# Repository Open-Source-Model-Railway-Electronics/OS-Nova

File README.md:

# OS-Nova

Initial repository skeleton.

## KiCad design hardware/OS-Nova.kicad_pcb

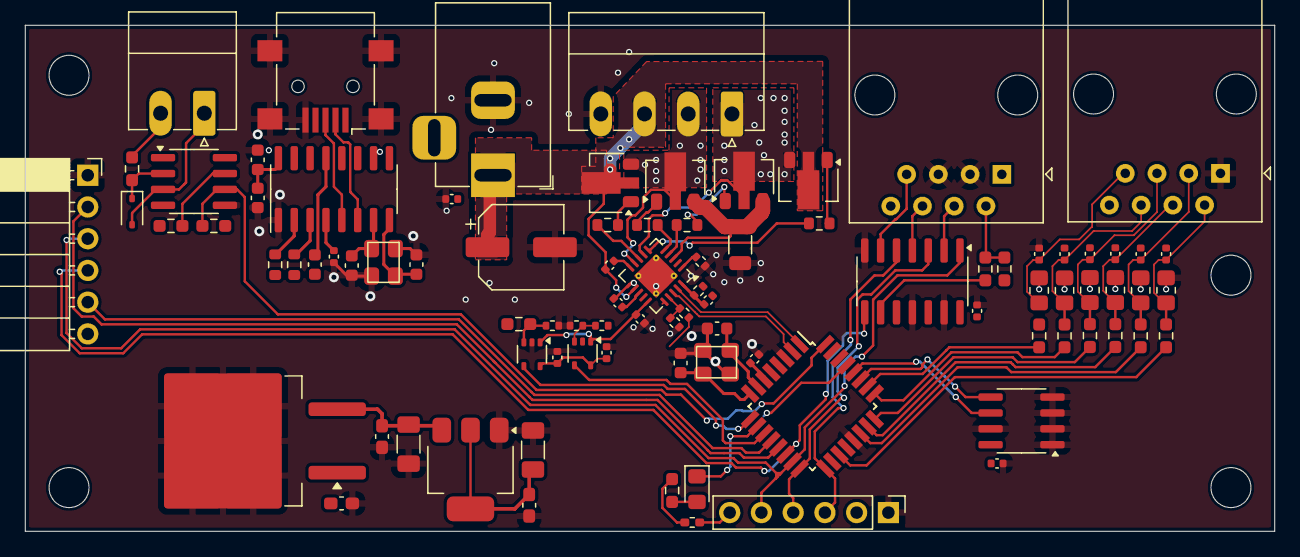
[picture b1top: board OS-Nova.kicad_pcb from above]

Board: 2 copper layers, 100.0 x 40.5 mm, 90 parts (0 on the bottom side), 73 nets.

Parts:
C201, C203: 12pF; C_0603_1608Metric
C202, C301, C501, C502, C503, C505, C506, C508, C604, C705, C707, C1001, C1201, C1301, C1401, C1801: 100nF; C_0402_1005Metric
C504: 1nF; C_0402_1005Metric
C507: 100uF; CP_Elec_6.3x7.7
C602, C802: 100nF; C_0603_1608Metric_Pad1.08x0.95mm_HandSolder
C603, C803: 100uF; C_1206_3216Metric_Pad1.33x1.80mm_HandSolder
C701: 10uF; C_0603_1608Metric
C702, C706: 100nF; C_0603_1608Metric
C703, C704: 22pF; C_0603_1608Metric
C801: 330nF; C_0603_1608Metric_Pad1.08x0.95mm_HandSolder
D201: LED; LED_0805_2012Metric_Pad1.15x1.40mm_HandSolder
D1701: 1N4148WS; D_SOD-323
J202: ICSP; PinHeader_1x06_P2.54mm_Vertical
J301, J401: RJ45; RJ45_Amphenol_54602-x08_Horizontal
J501: Screw_Terminal_01x04; PhoenixContact_MC_1,5_4-G-3.5_1x04_P3.50mm_Horizontal
J601: Jack-DC; BarrelJack_Horizontal
J701: USB_B_Mini; USB_Mini-B_Lumberg_2486_01_Horizontal
J901: Conn_01x06_Socket; PinSocket_1x06_P2.54mm_Horizontal
J1701: Screw_Terminal_01x02; PhoenixContact_MC_1,5_2-G-3.5_1x02_P3.50mm_Horizontal
Q501, Q502, Q503, Q504: TM10N06SI; SOT-89-3
R201: 6k2; R_0603_1608Metric_Pad0.98x0.95mm_HandSolder
R202: 10k; R_0402_1005Metric_Pad0.72x0.64mm_HandSolder
R301: 100R; R_0603_smalltext
R302: 4k7; R_0603_smalltext
R501, R502, R503, R504: 10R; R_0603_1608Metric
R505, R510: 22k; R_0402_1005Metric
R506: 10m; R_1206_3216Metric
R507: 150k; R_0402_1005Metric
R508, R512: 10k; R_0402_1005Metric
R509, R513: 1k; R_0402_1005Metric
R511: 62k; R_0603_smalltext
R601, R703, R1001, R1201, R1301, R1401: 1k; R_0603_smalltext
R602, R704, R1002, R1202, R1302, R1402: 250R; R_0805_handsolder-smalltext
R701, R702: 1k; R_0603_1608Metric
R1701, R1702: 10k; R_0603_smalltext
R1703: 1k5; R_0603_smalltext
U202: ATmega328-A; TQFP-32_7x7mm_P0.8mm
U301: 74HC14; SOIC-14_3.9x8.7mm_P1.27mm
U501: A4955; QFN-20-1EP_4x4mm_P0.5mm_EP2.5x2.5mm_ThermalVias
U502, U503: LMV321; SOT-353_SC-70-5
U701: CH340G; SOIC-16_3.9x9.9mm_P1.27mm
U801: L7812; TO-263-2
U802: AMS1117-5.0; SOT-223-3_TabPin2
U1701: HCPL-0601; SOIC-8_3.9x4.9mm_P1.27mm
U1801: 24LC256; SOIC-8_3.9x4.9mm_P1.27mm
Y201: Crystal_GND2; crystal_arduino
Y701: Crystal; crystal_arduino

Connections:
+5V: C202.1, C301.1, C503.2, C505.2, C602.1, C603.1, C701.1, C702.1, C1801.1, J202.2, J901.6, R201.1, R202.1, R302.1, R507.1, R509.1, R511.1, R1701.1, R1702.1, U202.4 (VCC), U202.6 (VCC), U202.18 (AVCC), U301.14 (VCC), U501.2 (SLEEPn), U502.5 (V+), U503.5 (V+), U701.16 (VCC), U802.2 (VO), U1701.8 (VCC), U1801.8 (VCC)
+12V: C802.1, C803.1, J301.1, J401.8, U801.3 (OUT), U802.3 (VI)
/CPU/CURRENT: U202.11 (PD7), U502.4
/CPU/DCC_TTL: R1701.2, U202.32 (PD2), U1701.6 (VO)
/CPU/J: U202.2 (PD4), U501.18 (IN2)
/CPU/K: U202.1 (PD3), U501.19 (IN1)
/CPU/LED: D201.1 (K), U202.10 (PD6)
/CPU/P1: R1001.1, U202.19 (ADC6)
/CPU/P2: R601.1, U202.22 (ADC7)
/CPU/P3: R703.1, U202.23 (PC0)
/CPU/P4: R1201.1, U202.24 (PC1)
/CPU/P5: R1301.1, U202.25 (PC2)
/CPU/P6: R1401.1, U202.26 (PC3)
/CPU/PL: J202.4, U202.16 (PB4), U301.3
/CPU/Reset: C706.2, J202.6, R202.2, U202.29 (~RESET/PC6)
/CPU/Rx: R701.2, U202.30 (PD0)
/CPU/S88RESET: J202.3, U202.17 (PB5), U301.5
/CPU/SCL: U202.28 (PC5), U1801.6 (SCL)
/CPU/SDA: U202.27 (PC4), U1801.5 (SDA)
/CPU/SHORT: U202.9 (PD5), U503.4
/CPU/Tx: R702.1, U202.31 (PD1)
/CPU/X1: C201.2, U202.7 (XTAL1/PB6), Y201.1
/CPU/X2: C203.2, U202.8 (XTAL2/PB7), Y201.3
/CPU/clock: J202.5, J901.3, U202.15 (PB3), U301.1
/CPU/in_next: J901.4, U202.14 (PB2), U301.8
/CPU/latch: J901.2, U202.13 (PB1)
/CPU/out_next: J901.5, U202.12 (PB0)
/DCC/AIOUT: C502.1, U501.15 (AIOUT), U502.1 (+), U503.1 (+)
/DCC/DCC_A: J501.2, Q501.3 (S), Q502.2 (D), U501.9 (SA)
/DCC/DCC_B: J501.1, Q503.3 (S), Q504.2 (D), U501.7 (SB)
/DCC/G_left_H: Q501.1 (G), R502.2
/DCC/G_left_L: Q502.1 (G), R501.2
/DCC/G_right_H: Q503.1 (G), R504.2
/DCC/G_right_L: Q504.1 (G), R503.2
/DCC/RETOUR: Q502.3 (S), Q504.3 (S), R506.1, U501.3 (SENSE)
/throttle/I-V-1/current: C1001.1, J401.2, R1001.2, R1002.1
/throttle/I-V-2/current: C604.1, J401.3, R601.2, R602.1
/throttle/I-V-3/current: C707.1, J401.4, R703.2, R704.1
/throttle/I-V-4/current: C1201.1, J401.5, R1201.2, R1202.1
/throttle/I-V-5/current: C1301.1, J401.6, R1301.2, R1302.1
/throttle/I-V-6/current: C1401.1, J401.7, R1401.2, R1402.1
GND: C201.1, C202.2, C203.1, C301.2, C502.2, C503.1, C504.1, C505.1, C506.2, C507.2, C602.2, C603.2, C604.2, C701.2, C702.2, C703.2, C704.2, C705.1, C707.2, C801.2, C802.2, C803.2, C1001.2, C1201.2, C1301.2, C1401.2, C1801.2, J202.1, J301.3, J301.5, J401.1, J501.4, J601.2, J701.5 (GND), J701.6 (Shield), J901.1, R505.2, R506.2, R508.2, R510.1, R512.2, R513.2, R602.2, R704.2, R1002.2, R1202.2, R1302.2, R1402.2, U202.3 (GND), U202.5 (GND), U202.21 (GND), U301.7 (GND), U301.11, U301.13, U501.14 (GND), U501.21 (GND), U502.2 (V-), U503.2 (V-), U701.1 (GND), U801.2 (GND), U802.1 (GND), U1701.5 (GND), U1801.1 (A0), U1801.2 (A1), U1801.3 (A2), U1801.4 (GND), U1801.7 (WP), Y201.2 (GND), Y201.4 (GND), Y701.2 (GND), Y701.4 (GND)
unnamed: D201.2 (A), R201.2
unnamed: D1701.2 (A), J1701.1, U1701.3 (C)
unnamed: D1701.1 (K), R1703.2, U1701.2 (A)
unnamed: J301.2, R301.2, R302.2
unnamed: J301.4, U301.2
unnamed: J301.6, U301.4
unnamed: J301.7, U301.6
unnamed: J701.3 (D+), U701.5 (UD+)
unnamed: J701.2 (D-), U701.6 (UD-)
unnamed: J1701.2, R1703.1
unnamed: R301.1, U301.9
unnamed: C508.2, U501.13 (CP1)
unnamed: C508.1, U501.11 (CP2)
unnamed: R502.1, U501.8 (GH_A)
unnamed: R504.1, U501.6 (GH_B)
unnamed: R501.1, U501.5 (GL_A)
unnamed: R503.1, U501.4 (GL_B)
unnamed: R505.1, U501.1 (Iset)
unnamed: C504.2, R510.2, U501.20 (RC)
unnamed: C501.1, U501.10 (VCP)
unnamed: R509.2, R513.1, U501.17 (VREF)
unnamed: R507.2, R508.1, U502.3 (-)
unnamed: R511.2, R512.1, U503.3 (-)
unnamed: R702.2, U701.3 (RXD)
unnamed: R701.1, U701.2 (TXD)
unnamed: C705.2, U701.4 (V3)
unnamed: C703.1, U701.7 (XI), Y701.1
unnamed: C704.1, U701.8 (XO), Y701.3
unnamed: C706.1, U701.13 (~DTR)
unnamed: R1702.2, U1701.7 (EN)
VCC: C501.2, C506.1, C507.1, C801.1, J501.3, J601.1, Q501.2 (D), Q503.2 (D), U501.12 (VBB), U801.1 (IN)

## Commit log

2025-12-09 added all files
2025-12-12 about to update loconet alot
2025-12-12 about to alter lcoonet py
2025-12-16 fixed a large portion of the route logic in command center software
    throttle.cpp now has some form of realtistic controls. Also implemented a digital variant for throttles.
    Instead of currents, digital throttles can send pulses at 20mA. Pulses are bitbanged in a similar way like with DCC.
    Also, the crappy python script will be replaced by a Qt6 application instead
